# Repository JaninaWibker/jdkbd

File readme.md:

The Jade keyboard is a split 40% ortholinear mechanical keyboard (*that's a lot of words*) which
(optionally) has a thinkpad trackpoint attachment on the right half.

> **WARNING**: THIS IS STILL IN DEVELOPMENT AND MIGHT BE COMPLETELY UNUSABLE

The red key represents the trackpoint [keyboard-layout-editor](http://www.keyboard-layout-editor.com/##@@_x:3&p=OEM&a:7%3B&=E&_x:6.5%3B&=I%3B&@_y:-0.75&x:2%3B&=W&_x:1%3B&=R&=T&_x:2.5%3B&=Y&=U&_x:1%3B&=O%3B&@_y:-0.75%3B&=&=Q&_x:10.5%3B&=P&=%3B&@_y:-0.5&x:3%3B&=D&_x:3.5&c=%23c45252&p=DSA&h2:1.25&l:true%3B&=&_x:2&c=%23cccccc&p=OEM%3B&=K%3B&@_y:-0.75&x:2%3B&=S&_x:1&n:true%3B&=F&=G&_x:2.5%3B&=H&_n:true%3B&=J&_x:1%3B&=L%3B&@_y:-0.75%3B&=&=A&_x:10.5%3B&=%5B&=%5D%3B&@_y:-0.5&x:3%3B&=C&_x:6.5%3B&=,%3B&@_y:-0.75&x:2%3B&=X&_x:1%3B&=V&=B&_x:2.5%3B&=N&=M&_x:1%3B&=.%3B&@_y:-0.75%3B&=&=Z&_x:10.5%3B&=-&=%3B&@_y:-0.25&x:2.75%3B&=&_x:7%3B&=%3B&@_y:-0.75%3B&=&_x:0.25%3B&=&_x:10%3B&=&=%3B&@_r:15&rx:7.25&ry:3.5&y:0.25&x:-2%3B&=%3B&@_y:-0.5&x:-3%3B&=%3B&@_ry:3.75&y:1&x:-2%3B&=%3B&@_r:-15&ry:3.5&y:0.25&x:1%3B&=%3B&@_y:-0.5&x:2%3B&=%3B&@_ry:3.75&y:1&x:1%3B&=)

<p align="center">
  
  <span>jdkbd without trackpoint</span>
</p>

The whole project is based on the [corne keyboard](https://github.com/foostan/crkbd) by foostan but
has undergone many modifications. Still, a lot of work has been saved duo to the work done
by foostan.

The main differences between the corne and the jade are that:
- corne has 4 less keys (44 vs 48; jade has a bottom row and thumb cluster while the corne only has
  a thumb cluster)
- corne is (depending on the model) reversible; the jade uses kailh hot-swap sockets which are also
  supported by the corne-cherry version (which is also not reversible)
- corne has more case options available, the jade currently only has "pcb case"

## Getting the keyboard

The current method to getting a jade keyboard is letting it be manufactured by jlcpcb, pcbway or a
different pcb manufacturer. There are no kits available.

> Almost all pcb manufacturers have a minimum order quantity of 5pc; getting 5 times the pieces you
> need might still be cheaper than some other keyboard kits and you can possibly resell them.

The keyboard comes in 3 different parts: the pcb, the bottom plate and the top plate.

## Building and needed components

You mainly need kailh hot-swap sockets, screws, LEDs and ProMicro's

The full list can be found [here](/components.md) along with some cost estimates.

Build instructions can be found [here](/build-instructions.md).

## Modifying the keyboard

The keyboard was designed in [KiCad](https://https://kicad-pcb.org/) and uses some of
[foostan's footprints / symbols](https://github.com/foostan/kbd) for custom keyboards, as well as a few
standard KiCad libraries (power & led).

These should be directly available when cloning the repo **with submodules**. This can be done by
using

```sh
git clone --recursive [url]
```

when cloning the repo initially or later on using

```sh
git submodule update --init --recursive
```

A few beginner mistakes I made / faced are:
- not working with eeschema and jumping straight into pcbnew (the pcb designer)
- not caring about aligning things to the grid (KiCad really likes it's grid)

Make sure that the paths for the additional symbols and footprints are configured correctly. It should
look something like this:

footprints: 

| nickname | library path                                    |
| -------- | ----------------------------------------------- |
| kbd      | `${KIPRJMOD}/kbd/kicad-footprints/kbd.pretty`   |
| logo     | `${KIPRJMOD}/../logo-footprints`                |

symbols:

| nickname | library path                                    |
| -------- | ----------------------------------------------- |
| kbd      | `${KIPRJMOD}/kbd/kicad-symbols/kbd.lib`         |
| power    | `${KIPRJMOD}/libraries/kicad-symbols/power.lib` |
| LED      | `${KIPRJMOD}/libraries/kicad-symbols/LED.lib`   |

When using KiCad 5.1.6 the pick and place file (also called .pos file) might be incorrect. Using
later versions will probably fix this as well as prior versions as this is a bug that was introduced
while fixing another bug.

Incase you are using KiCad 5.1.6 the error is easy to correct: the x-coordinate in the (csv) file is
simply flipped. Just flip it back and you are fine.

If you are using JLCPCB for manufacturing you can use their preview while ordering to check that everything
is alright. 

> Modifying the PCB can require also modifying the bottom- and top-plate.

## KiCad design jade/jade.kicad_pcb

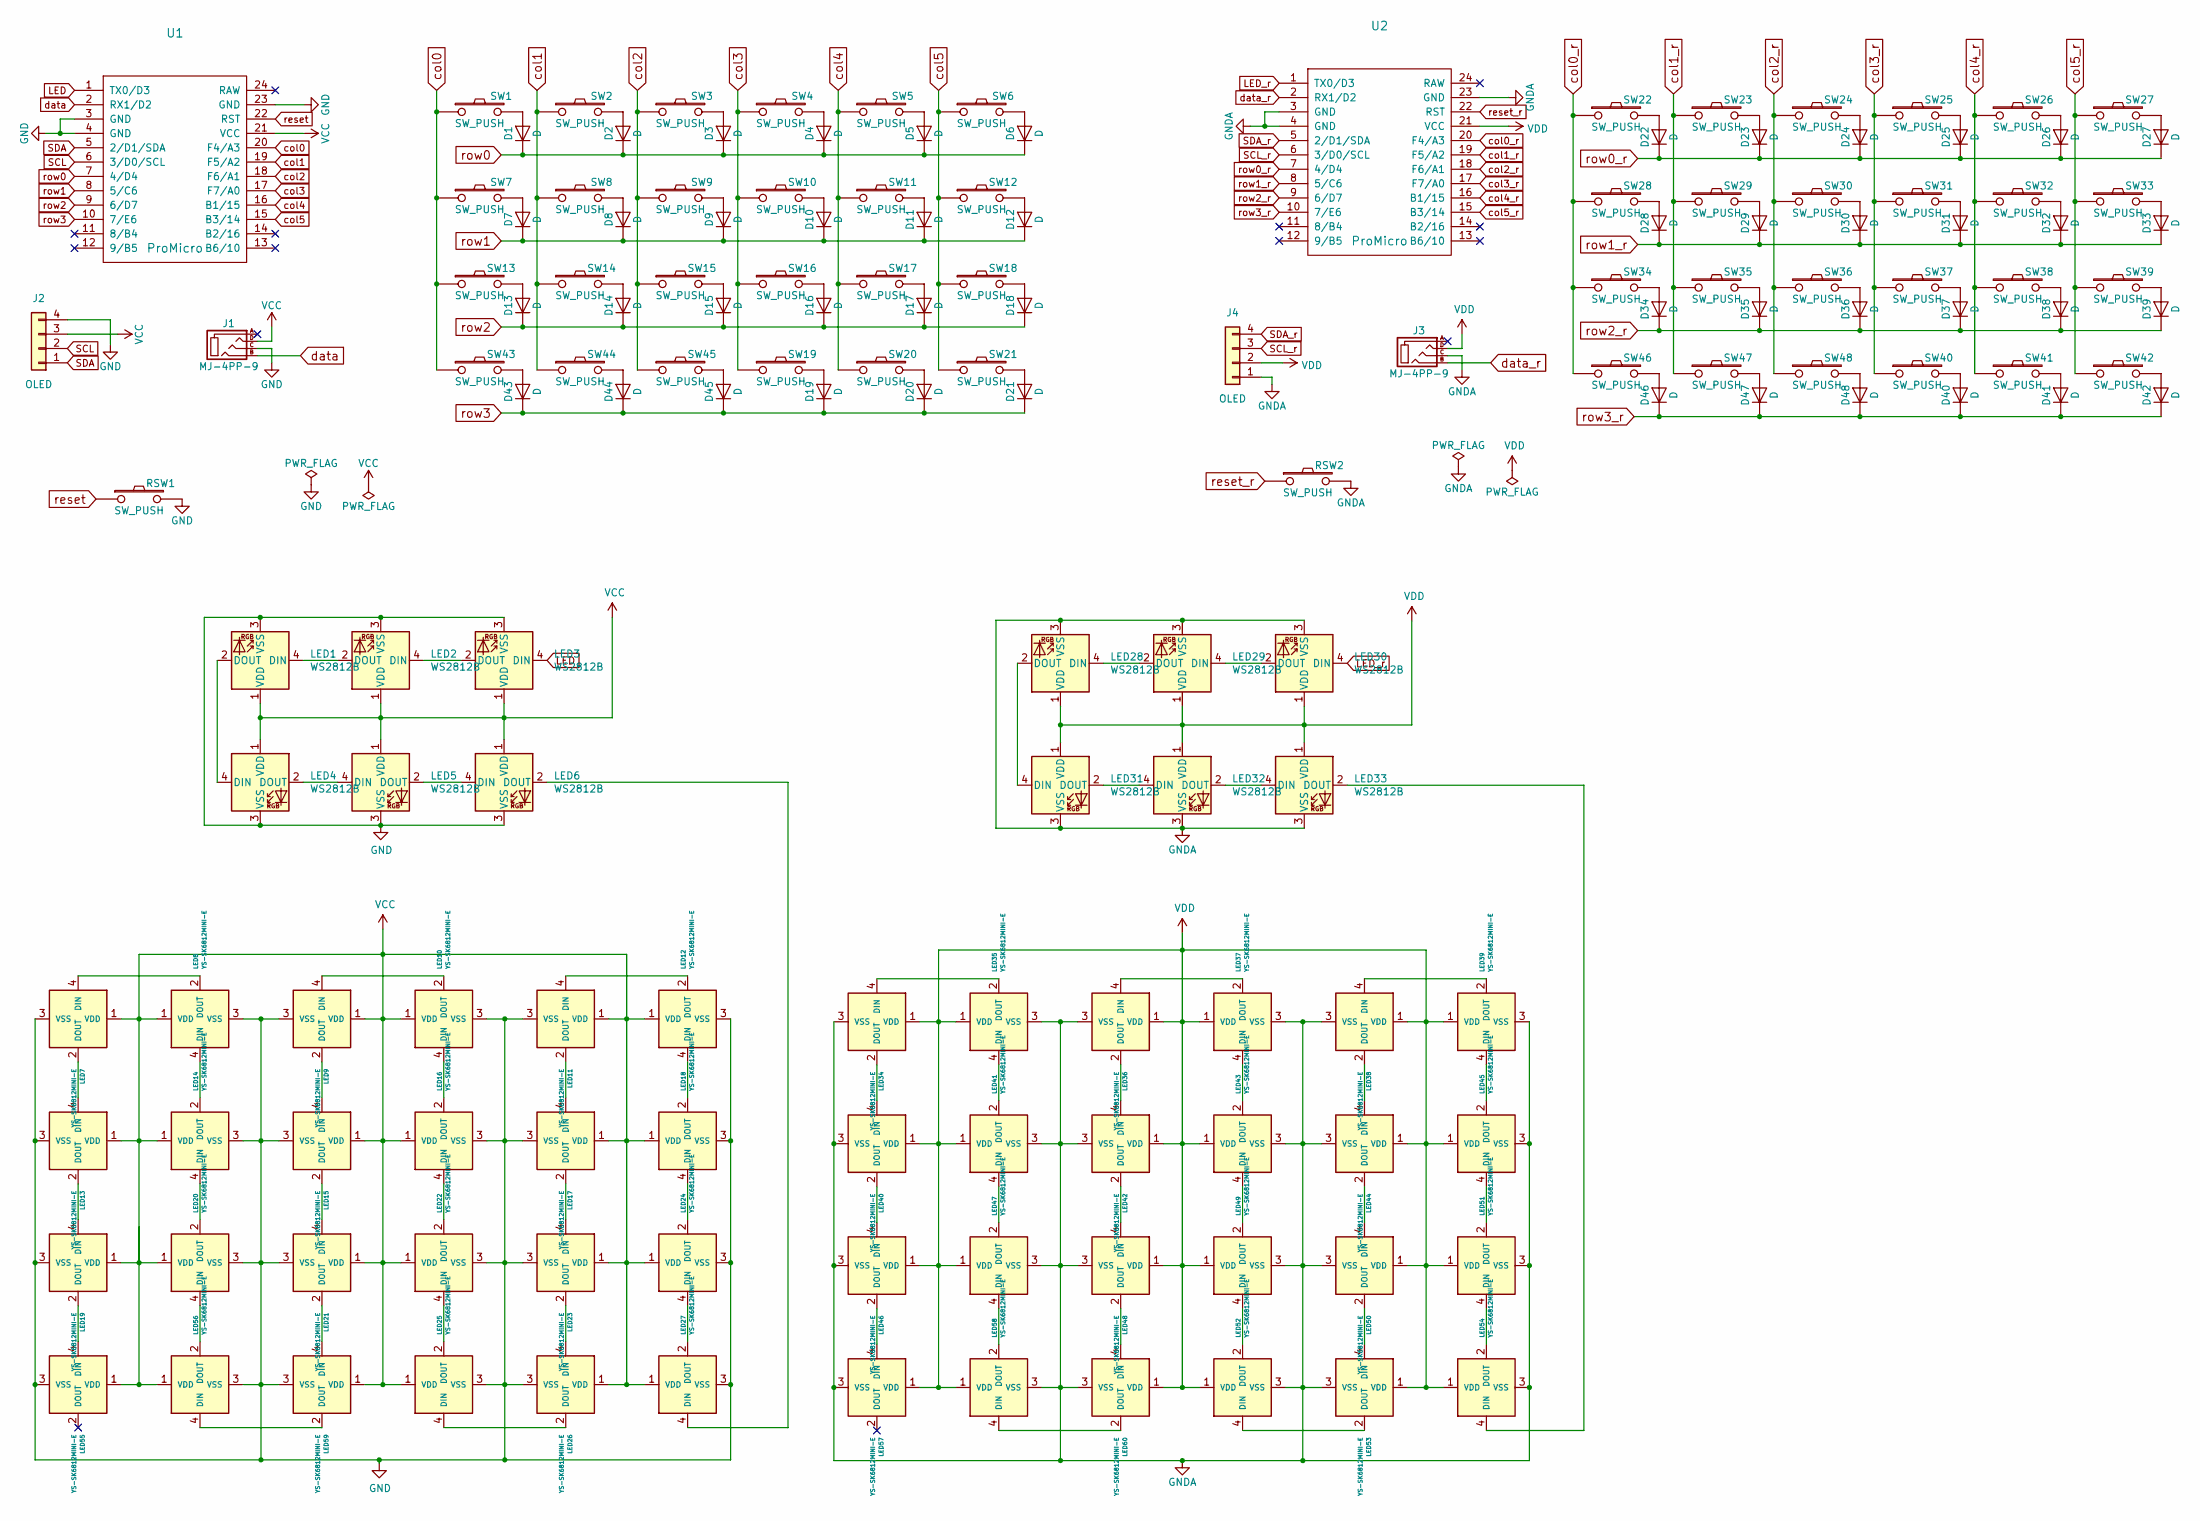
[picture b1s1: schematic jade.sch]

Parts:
D1, D2, D3, D4, D5, D6, D7, D8, D9, D10, D11, D12, D13, D14, D15, D16, D17, D18, D19, D20, D21, D22, D23, D24, D25, D26, D27, D28, D29, D30, D31, D32, D33, D34, D35, D36, D37, D38, D39, D40, D41, D42, D43, D44, D45, D46, D47, D48: D; D3_SMD_v2; LCSC Part # C81598
J1, J3: MJ-4PP-9; MJ-4PP-9_1side
J2, J4: OLED; OLED_1side
LED1, LED2, LED3, LED4, LED5, LED6, LED28, LED29, LED30, LED31, LED32, LED33: WS2812B; LED_WS2812B_PLCC4_5.0x5.0mm_P3.2mm; LCSC Part # C114586
LED7, LED8, LED9, LED10, LED11, LED12, LED13, LED14, LED15, LED16, LED17, LED18, LED19, LED20, LED21, LED22, LED23, LED24, LED25, LED26, LED27, LED34, LED35, LED36, LED37, LED38, LED39, LED40, LED41, LED42, LED43, LED44, LED45, LED46, LED47, LED48, LED49, LED50, LED51, LED52, LED53, LED54, LED55, LED56, LED57, LED58, LED59, LED60: YS-SK6812MINI-E
RSW1, RSW2: SW_PUSH; ResetSW_1side
SW1, SW2, SW3, SW4, SW5, SW6, SW7, SW8, SW9, SW10, SW11, SW12, SW13, SW14, SW15, SW16, SW17, SW18, SW19, SW20, SW22, SW23, SW24, SW25, SW26, SW27, SW28, SW29, SW30, SW31, SW32, SW33, SW34, SW35, SW36, SW37, SW38, SW39, SW40, SW41, SW43, SW44, SW45, SW46, SW47, SW48: SW_PUSH; CherryMX_Hotswap
SW21, SW42: SW_PUSH; CherryMX_Hotswap_1.5u
U1, U2: ProMicro; ProMicro_v2_1side

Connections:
GND: J1.C, J2.4, LED1.3 (VSS), LED2.3 (VSS), LED3.3 (VSS), LED4.3 (VSS), LED5.3 (VSS), LED6.3 (VSS), LED7.3 (VSS), LED8.3 (VSS), LED9.3 (VSS), LED10.3 (VSS), LED11.3 (VSS), LED12.3 (VSS), LED13.3 (VSS), LED14.3 (VSS), LED15.3 (VSS), LED16.3 (VSS), LED17.3 (VSS), LED18.3 (VSS), LED19.3 (VSS), LED20.3 (VSS), LED21.3 (VSS), LED22.3 (VSS), LED23.3 (VSS), LED24.3 (VSS), LED25.3 (VSS), LED26.3 (VSS), LED27.3 (VSS), LED55.3 (VSS), LED56.3 (VSS), LED59.3 (VSS), RSW1.2, U1.3 (GND), U1.4 (GND), U1.23 (GND)
GNDA: J3.C, J4.1, LED28.3 (VSS), LED29.3 (VSS), LED30.3 (VSS), LED31.3 (VSS), LED32.3 (VSS), LED33.3 (VSS), LED34.3 (VSS), LED35.3 (VSS), LED36.3 (VSS), LED37.3 (VSS), LED38.3 (VSS), LED39.3 (VSS), LED40.3 (VSS), LED41.3 (VSS), LED42.3 (VSS), LED43.3 (VSS), LED44.3 (VSS), LED45.3 (VSS), LED46.3 (VSS), LED47.3 (VSS), LED48.3 (VSS), LED49.3 (VSS), LED50.3 (VSS), LED51.3 (VSS), LED52.3 (VSS), LED53.3 (VSS), LED54.3 (VSS), LED57.3 (VSS), LED58.3 (VSS), LED60.3 (VSS), RSW2.2, U2.3 (GND), U2.4 (GND), U2.23 (GND)
LED: LED3.4 (DIN), U1.1 (TX0/D3)
LED_r: LED30.4 (DIN), U2.1 (TX0/D3)
unnamed: D1.2 (A), SW1.2
unnamed: D2.2 (A), SW2.2
unnamed: D3.2 (A), SW3.2
unnamed: D4.2 (A), SW4.2
unnamed: D5.2 (A), SW5.2
unnamed: D6.2 (A), SW6.2
unnamed: D7.2 (A), SW7.2
unnamed: D8.2 (A), SW8.2
unnamed: D9.2 (A), SW9.2
unnamed: D10.2 (A), SW10.2
unnamed: D11.2 (A), SW11.2
unnamed: D12.2 (A), SW12.2
unnamed: D13.2 (A), SW13.2
unnamed: D14.2 (A), SW14.2
unnamed: D15.2 (A), SW15.2
unnamed: D16.2 (A), SW16.2
unnamed: D17.2 (A), SW17.2
unnamed: D18.2 (A), SW18.2
unnamed: D19.2 (A), SW19.2
unnamed: D20.2 (A), SW20.2
unnamed: D21.2 (A), SW21.2
unnamed: D22.2 (A), SW22.2
unnamed: D23.2 (A), SW23.2
unnamed: D24.2 (A), SW24.2
unnamed: D25.2 (A), SW25.2
unnamed: D26.2 (A), SW26.2
unnamed: D27.2 (A), SW27.2
unnamed: D28.2 (A), SW28.2
unnamed: D29.2 (A), SW29.2
unnamed: D30.2 (A), SW30.2
unnamed: D31.2 (A), SW31.2
unnamed: D32.2 (A), SW32.2
unnamed: D33.2 (A), SW33.2
unnamed: D34.2 (A), SW34.2
unnamed: D35.2 (A), SW35.2
unnamed: D36.2 (A), SW36.2
unnamed: D37.2 (A), SW37.2
unnamed: D38.2 (A), SW38.2
unnamed: D39.2 (A), SW39.2
unnamed: D40.2 (A), SW40.2
unnamed: D41.2 (A), SW41.2
unnamed: D42.2 (A), SW42.2
unnamed: D43.2 (A), SW43.2
unnamed: D44.2 (A), SW44.2
unnamed: D45.2 (A), SW45.2
unnamed: D46.2 (A), SW46.2
unnamed: D47.2 (A), SW47.2
unnamed: D48.2 (A), SW48.2
unnamed: LED1.2 (DOUT), LED4.4 (DIN)
unnamed: LED1.4 (DIN), LED2.2 (DOUT)
unnamed: LED2.4 (DIN), LED3.2 (DOUT)
unnamed: LED4.2 (DOUT), LED5.4 (DIN)
unnamed: LED5.2 (DOUT), LED6.4 (DIN)
unnamed: LED7.4 (DIN), LED8.2 (DOUT)
unnamed: LED9.4 (DIN), LED10.2 (DOUT)
unnamed: LED10.4 (DIN), LED16.2 (DOUT)
unnamed: LED11.2 (DOUT), LED17.4 (DIN)
unnamed: LED11.4 (DIN), LED12.2 (DOUT)
unnamed: LED12.4 (DIN), LED18.2 (DOUT)
unnamed: LED13.2 (DOUT), LED19.4 (DIN)
unnamed: LED7.2 (DOUT), LED13.4 (DIN)
unnamed: LED8.4 (DIN), LED14.2 (DOUT)
unnamed: LED14.4 (DIN), LED20.2 (DOUT)
unnamed: LED15.2 (DOUT), LED21.4 (DIN)
unnamed: LED9.2 (DOUT), LED15.4 (DIN)
unnamed: LED16.4 (DIN), LED22.2 (DOUT)
unnamed: LED17.2 (DOUT), LED23.4 (DIN)
unnamed: LED18.4 (DIN), LED24.2 (DOUT)
unnamed: LED19.2 (DOUT), LED55.4 (DIN)
unnamed: LED20.4 (DIN), LED56.2 (DOUT)
unnamed: LED21.2 (DOUT), LED59.4 (DIN)
unnamed: LED22.4 (DIN), LED25.2 (DOUT)
unnamed: LED23.2 (DOUT), LED26.4 (DIN)
unnamed: LED24.4 (DIN), LED27.2 (DOUT)
unnamed: LED25.4 (DIN), LED26.2 (DOUT)
unnamed: LED6.2 (DOUT), LED27.4 (DIN)
unnamed: LED28.2 (DOUT), LED31.4 (DIN)
unnamed: LED28.4 (DIN), LED29.2 (DOUT)
unnamed: LED29.4 (DIN), LED30.2 (DOUT)
unnamed: LED31.2 (DOUT), LED32.4 (DIN)
unnamed: LED32.2 (DOUT), LED33.4 (DIN)
unnamed: LED33.2 (DOUT), LED54.4 (DIN)
unnamed: LED34.2 (DOUT), LED40.4 (DIN)
unnamed: LED34.4 (DIN), LED35.2 (DOUT)
unnamed: LED35.4 (DIN), LED41.2 (DOUT)
unnamed: LED36.2 (DOUT), LED42.4 (DIN)
unnamed: LED36.4 (DIN), LED37.2 (DOUT)
unnamed: LED37.4 (DIN), LED43.2 (DOUT)
unnamed: LED38.2 (DOUT), LED44.4 (DIN)
unnamed: LED38.4 (DIN), LED39.2 (DOUT)
unnamed: LED39.4 (DIN), LED45.2 (DOUT)
unnamed: LED40.2 (DOUT), LED46.4 (DIN)
unnamed: LED41.4 (DIN), LED47.2 (DOUT)
unnamed: LED42.2 (DOUT), LED48.4 (DIN)
unnamed: LED43.4 (DIN), LED49.2 (DOUT)
unnamed: LED44.2 (DOUT), LED50.4 (DIN)
unnamed: LED45.4 (DIN), LED51.2 (DOUT)
unnamed: LED46.2 (DOUT), LED57.4 (DIN)
unnamed: LED47.4 (DIN), LED58.2 (DOUT)
unnamed: LED48.2 (DOUT), LED60.4 (DIN)
unnamed: LED49.4 (DIN), LED52.2 (DOUT)
unnamed: LED50.2 (DOUT), LED53.4 (DIN)
unnamed: LED51.4 (DIN), LED54.2 (DOUT)
unnamed: LED52.4 (DIN), LED53.2 (DOUT)
unnamed: LED56.4 (DIN), LED59.2 (DOUT)
unnamed: LED58.4 (DIN), LED60.2 (DOUT)
SCL: J2.2, U1.6 (3/D0/SCL)
SCL_r: J4.3, U2.6 (3/D0/SCL)
SDA: J2.1, U1.5 (2/D1/SDA)
SDA_r: J4.4, U2.5 (2/D1/SDA)
VCC: J1.D, J2.3, LED1.1 (VDD), LED2.1 (VDD), LED3.1 (VDD), LED4.1 (VDD), LED5.1 (VDD), LED6.1 (VDD), LED7.1 (VDD), LED8.1 (VDD), LED9.1 (VDD), LED10.1 (VDD), LED11.1 (VDD), LED12.1 (VDD), LED13.1 (VDD), LED14.1 (VDD), LED15.1 (VDD), LED16.1 (VDD), LED17.1 (VDD), LED18.1 (VDD), LED19.1 (VDD), LED20.1 (VDD), LED21.1 (VDD), LED22.1 (VDD), LED23.1 (VDD), LED24.1 (VDD), LED25.1 (VDD), LED26.1 (VDD), LED27.1 (VDD), LED55.1 (VDD), LED56.1 (VDD), LED59.1 (VDD), U1.21 (VCC)
VDD: J3.D, J4.2, LED28.1 (VDD), LED29.1 (VDD), LED30.1 (VDD), LED31.1 (VDD), LED32.1 (VDD), LED33.1 (VDD), LED34.1 (VDD), LED35.1 (VDD), LED36.1 (VDD), LED37.1 (VDD), LED38.1 (VDD), LED39.1 (VDD), LED40.1 (VDD), LED41.1 (VDD), LED42.1 (VDD), LED43.1 (VDD), LED44.1 (VDD), LED45.1 (VDD), LED46.1 (VDD), LED47.1 (VDD), LED48.1 (VDD), LED49.1 (VDD), LED50.1 (VDD), LED51.1 (VDD), LED52.1 (VDD), LED53.1 (VDD), LED54.1 (VDD), LED57.1 (VDD), LED58.1 (VDD), LED60.1 (VDD), U2.21 (VCC)
col0: SW1.1, SW7.1, SW13.1, SW43.1, U1.20 (F4/A3)
col0_r: SW22.1, SW28.1, SW34.1, SW46.1, U2.20 (F4/A3)
col1: SW2.1, SW8.1, SW14.1, SW44.1, U1.19 (F5/A2)
col1_r: SW23.1, SW29.1, SW35.1, SW47.1, U2.19 (F5/A2)
col2: SW3.1, SW9.1, SW15.1, SW45.1, U1.18 (F6/A1)
col2_r: SW24.1, SW30.1, SW36.1, SW48.1, U2.18 (F6/A1)
col3: SW4.1, SW10.1, SW16.1, SW19.1, U1.17 (F7/A0)
col3_r: SW25.1, SW31.1, SW37.1, SW40.1, U2.17 (F7/A0)
col4: SW5.1, SW11.1, SW17.1, SW20.1, U1.16 (B1/15)
col4_r: SW26.1, SW32.1, SW38.1, SW41.1, U2.16 (B1/15)
col5: SW6.1, SW12.1, SW18.1, SW21.1, U1.15 (B3/14)
col5_r: SW27.1, SW33.1, SW39.1, SW42.1, U2.15 (B3/14)
data: J1.B, U1.2 (RX1/D2)
data_r: J3.B, U2.2 (RX1/D2)
reset: RSW1.1, U1.22 (RST)
reset_r: RSW2.1, U2.22 (RST)
row0: D1.1 (K), D2.1 (K), D3.1 (K), D4.1 (K), D5.1 (K), D6.1 (K), U1.7 (4/D4)
row0_r: D22.1 (K), D23.1 (K), D24.1 (K), D25.1 (K), D26.1 (K), D27.1 (K), U2.7 (4/D4)
row1: D7.1 (K), D8.1 (K), D9.1 (K), D10.1 (K), D11.1 (K), D12.1 (K), U1.8 (5/C6)
row1_r: D28.1 (K), D29.1 (K), D30.1 (K), D31.1 (K), D32.1 (K), D33.1 (K), U2.8 (5/C6)
row2: D13.1 (K), D14.1 (K), D15.1 (K), D16.1 (K), D17.1 (K), D18.1 (K), U1.9 (6/D7)
row2_r: D34.1 (K), D35.1 (K), D36.1 (K), D37.1 (K), D38.1 (K), D39.1 (K), U2.9 (6/D7)
row3: D19.1 (K), D20.1 (K), D21.1 (K), D43.1 (K), D44.1 (K), D45.1 (K), U1.10 (7/E6)
row3_r: D40.1 (K), D41.1 (K), D42.1 (K), D46.1 (K), D47.1 (K), D48.1 (K), U2.10 (7/E6)

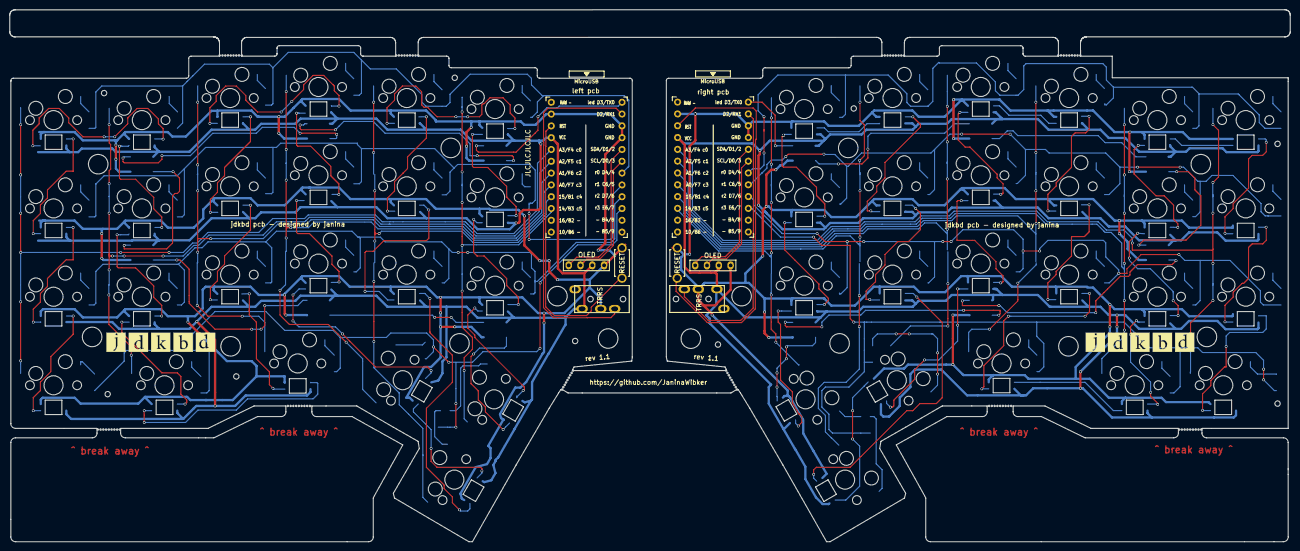
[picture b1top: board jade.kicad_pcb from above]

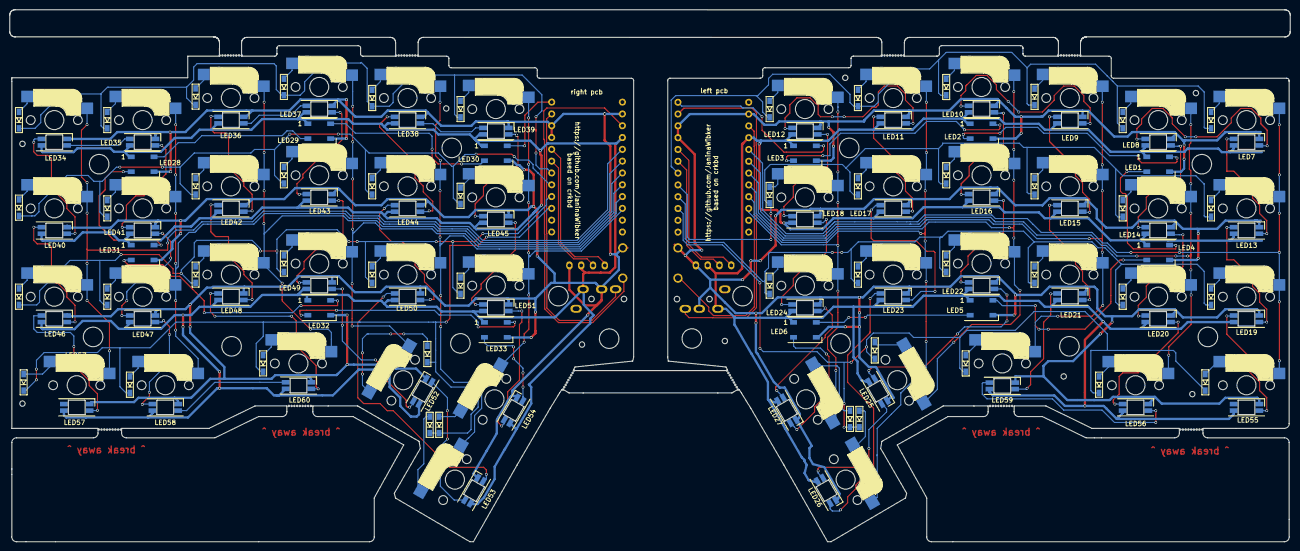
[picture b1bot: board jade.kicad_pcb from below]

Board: 2 copper layers, 275.5 x 114.5 mm, 178 parts (115 on the bottom side), 140 nets.

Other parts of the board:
Ref**: Val**; M2_HOLE_v2
Ref**#2, Ref**#3, Ref**#4, Ref**#5, Ref**#6, Ref**#7, Ref**#8, Ref**#9, Ref**#10, Ref**#11, Ref**#12, Ref**#13, Ref**#14: Val**; M2_HOLE_v2

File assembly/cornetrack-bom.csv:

Comment,Designator,Footprint,LCSC
"D","D1,D2,D3,D4,D5,D6,D7,D8,D9,D10,D11,D12,D13,D14,D15,D16,D17,D18,D19,D20,D21,D22,D23,D24,D25,D26,D27,D28,D29,D30,D31,D32,D33,D34,D35,D36,D37,D38,D39,D40,D41,D42,D43,D44,D45,D46,D47,D48","kbd:D3_SMD_v2","C81598"
"MJ-4PP-9","J1,J3","kbd:MJ-4PP-9_1side",""
"OLED","J2,J4","kbd:OLED_1side",""
"WS2812B","LED1,LED2,LED3,LED4,LED5,LED6,LED28,LED29,LED30,LED31,LED32,LED33","LED_SMD:LED_WS2812B_PLCC4_5.0x5.0mm_P3.2mm","C114586"
"YS-SK6812MINI-E","LED7,LED8,LED9,LED10,LED11,LED12,LED13,LED14,LED15,LED16,LED17,LED18,LED19,LED20,LED21,LED22,LED23,LED24,LED25,LED26,LED27,LED34,LED35,LED36,LED37,LED38,LED39,LED40,LED41,LED42,LED43,LED44,LED45,LED46,LED47,LED48,LED49,LED50,LED51,LED52,LED53,LED54,LED55,LED56,LED57,LED58,LED59,LED60","kbd:YS-SK6812MINI-E","
"SW_PUSH","RSW1,RSW2","kbd:ResetSW_1side",""
"SW_PUSH","SW1,SW2,SW3,SW4,SW5,SW6,SW7,SW8,SW9,SW10,SW11,SW12,SW13,SW14,SW15,SW16,SW17,SW18,SW19,SW20,SW22,SW23,SW24,SW25,SW26,SW27,SW28,SW29,SW30,SW31,SW32,SW33,SW34,SW35,SW36,SW37,SW38,SW39,SW40,SW41,SW43,SW44,SW45,SW46,SW47,SW48","kbd:CherryMX_Hotswap",""
"SW_PUSH","SW21,SW42","kbd:CherryMX_Hotswap_1.5u",""
"ProMicro","U1,U2","kbd:ProMicro_v2_1side",""

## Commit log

2020-09-23 added parts list
2020-09-27 finished pcb design; minor improvements are still to be expected
2020-09-28 updated schematic and pcb
    schematic: fixed unconnected pins and aligned some components to the grid
    pcb: updated wires according to new schematic, created outline (edge
    cuts layer), added a few more labels, fixed a few smaller mistakes
2020-09-28 added gerber files and added even more lables to the pcb
2020-09-28 added zip of gerber files and assembly related files
2020-09-29 renamed project, diode rotation, assembly - renamed project from corne-cherry to cornetrack - tried to have all diodes rotated the same way - did numerous assembly related shenanigans; this is all in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
2020-09-29 added bottom-plate as subproject (has no real schematic; only pcb)
2020-09-30 regenerated gerber files
2020-09-30 made all holes and almost all diodes on both pcbs symmetric to each other (meaning that accidentally having all coordinates in the .pos file inverted would not cause a big problem for almost all of t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
2020-09-30 added top-plate (works for both sides / pcbs)
2020-09-30 created a logo; wrote a short readme; decided on the name "Jade" (or jdkbd for jade keyboard)
2020-09-30 moved almost everything into the new jade directory
2020-10-01 added logos on silkscreen and plotted all gerber files again
2020-10-01 moved tracks further away from edges
2020-10-05 made top and bottom plate a tiny bit larger in order to increase distance between edge cuts to >2mm
2020-10-05 added list of needed components (probably somewhat incomplete)
2020-10-05 changed name again (cornetrack -> jade)
2020-10-05 added MIT license and corrected small readme mistake
2020-10-05 added image of keyboard layout
2020-10-05 deleted unused kbd2 folder
2020-10-05 added warning about the whole project being WIP
2020-10-29 added breakout tabs and made pcb mostly rectangular
2020-10-30 added "break away" text to break away thingies
2020-10-31 added missing drill files :/
2020-11-07 fixed small mistake in component list
2021-02-25 added an image
2025-03-14 update things
